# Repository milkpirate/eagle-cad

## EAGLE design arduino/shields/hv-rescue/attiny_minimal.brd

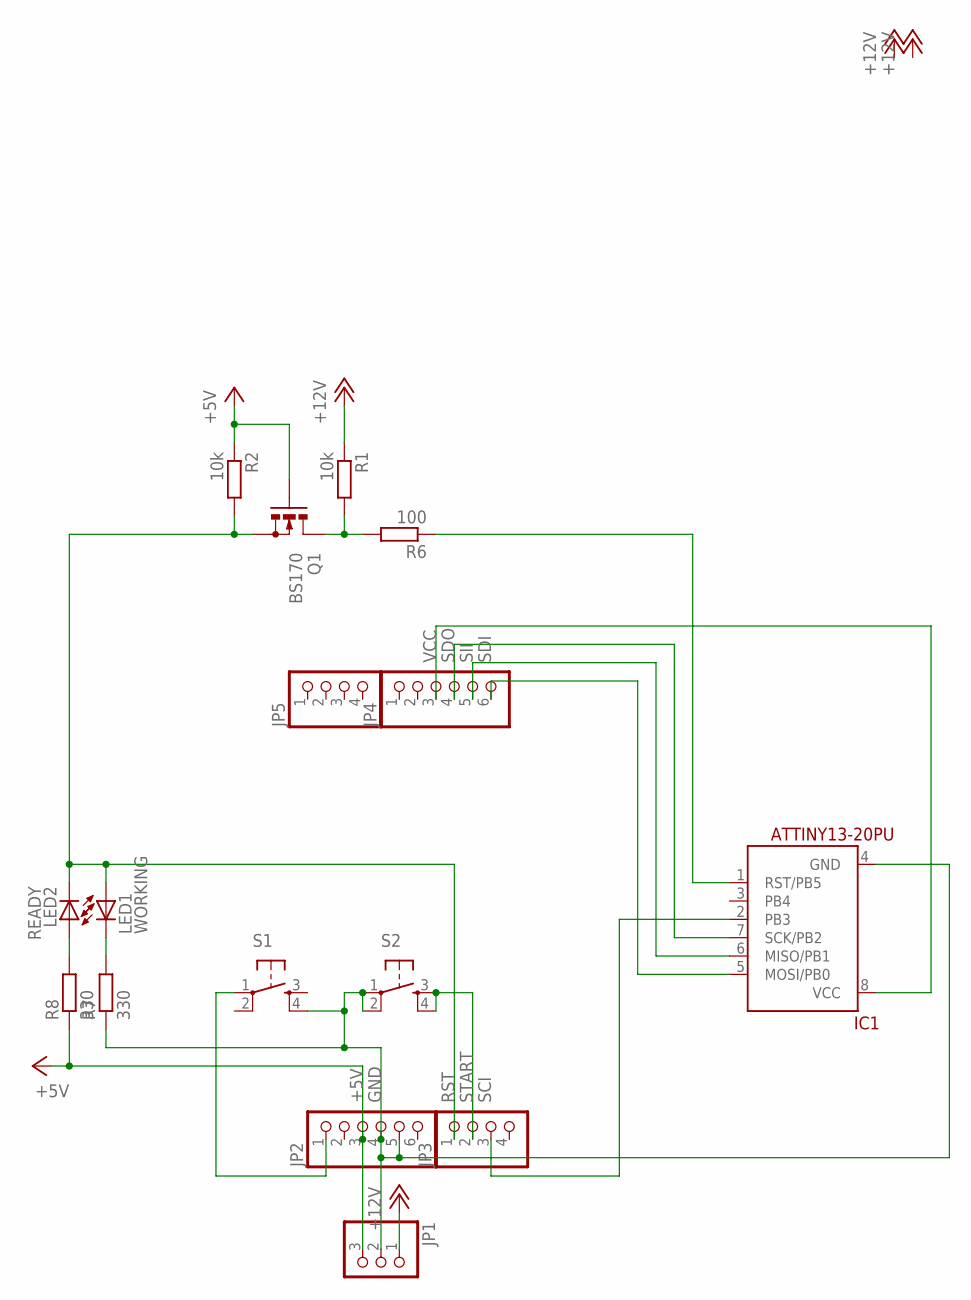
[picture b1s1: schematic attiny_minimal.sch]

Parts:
IC1: ATTINY13-20PU; DIL08
JP1: PINHD-1X3/90; 1X03/90
JP2, JP4: PINHD-1X6; 1X06
JP3, JP5: PINHD-1X4; 1X04
LED1: WORKING; LED3MM
LED2: READY; LED3MM
Q1: BS170; SOT54E
R1: 10k; 0207/2V
R2: 10k; 0204/7
R6: 100; 0204/7
R7, R8: 330; 0207/2V
S1, S2: TAC_SWITCHPTH; TACTILE-PTH

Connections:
+5V: JP1.3, JP2.3, Q1.G, R2.1, R8.1
+12V: JP1.1, R1.1
GND: IC1.4 (GND), JP1.2, JP2.4, JP2.5, R7.1, S1.4, S2.1, S2.2
unnamed: JP2.1, S1.1
unnamed: LED1.K (C), R7.2
unnamed: LED2.A, R8.2
unnamed: Q1.D, R1.2, R6.2
unnamed: IC1.1 (RST/PB5), R6.1
RST: JP3.1, LED1.A, LED2.K (C), Q1.S, R2.2
SCI: IC1.2 (PB3), JP3.3
SDI: IC1.5 (MOSI/PB0), JP4.6
SDO: IC1.7 (SCK/PB2), JP4.4
SII: IC1.6 (MISO/PB1), JP4.5
START: JP3.2, S2.3, S2.4
VCC: IC1.8 (VCC), JP4.3

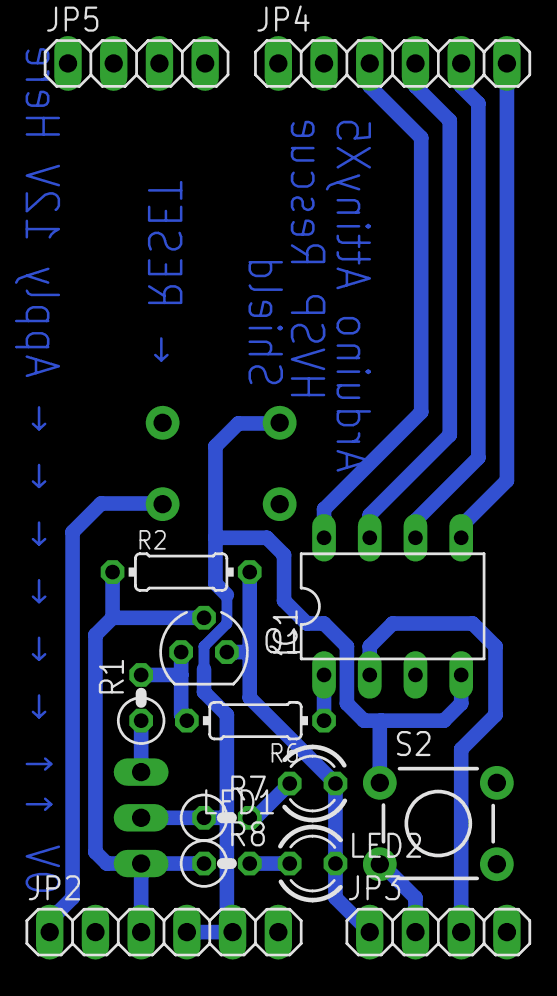
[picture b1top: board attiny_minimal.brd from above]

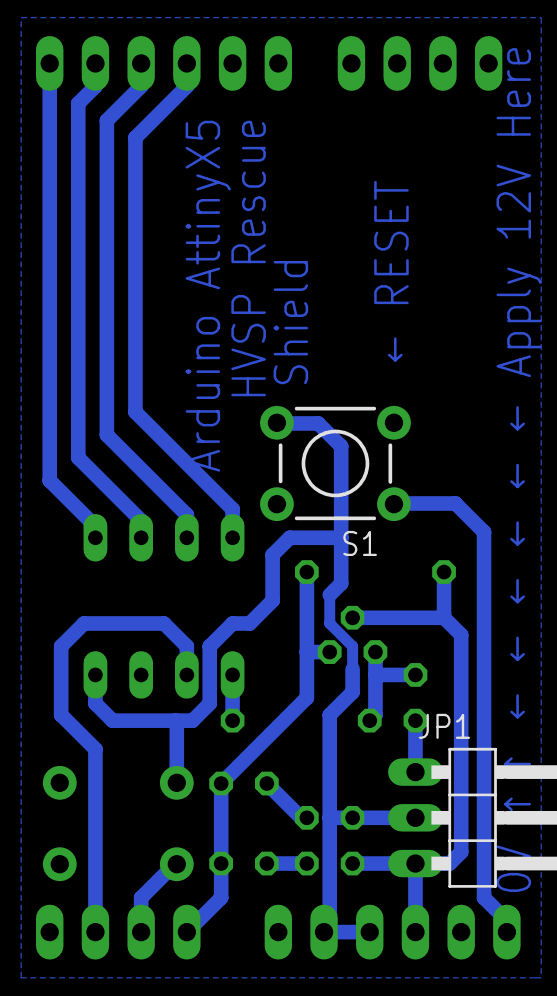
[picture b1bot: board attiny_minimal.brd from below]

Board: 2 copper layers, 16 parts (2 on the bottom side), 15 nets.

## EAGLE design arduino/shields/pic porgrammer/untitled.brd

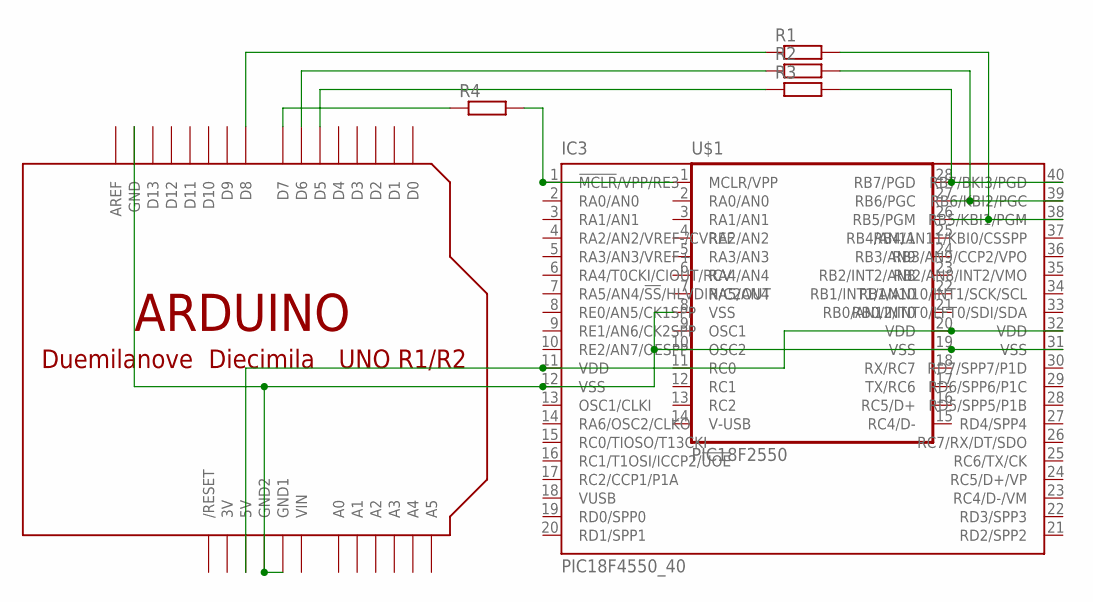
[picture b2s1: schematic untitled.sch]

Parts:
IC3: PIC18F4550_40; DIL40
R1, R2, R3, R4: R-EU_0204/7; 0204/7
U$1: PIC18F2550; DIL28-3
U$2: ARDUINO-NOHOLE

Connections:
3V: U$2.3V
GND: IC3.12 (VSS), IC3.31 (VSS), U$1.8 (VSS), U$1.19 (VSS), U$2.GND, U$2.GND1, U$2.GND2
unnamed: IC3.1 (!MCLR!/VPP/RE3), R4.2, U$1.1 (MCLR/VPP)
unnamed: IC3.40 (RB7/BKI3/PGD), R3.2, U$1.28 (RB7/PGD)
unnamed: IC3.39 (RB6/KBI2/PGC), R2.2, U$1.27 (RB6/PGC)
unnamed: IC3.38 (RB5/KBI1/PGM), R1.2, U$1.26 (RB5/PGM)
unnamed: IC3.11 (VDD), IC3.32 (VDD), U$1.20 (VDD), U$2.5V
unnamed: R1.1, U$2.D8
unnamed: R2.1, U$2.D6
unnamed: R3.1, U$2.D5
unnamed: R4.1, U$2.D7
VIN: U$2.VIN

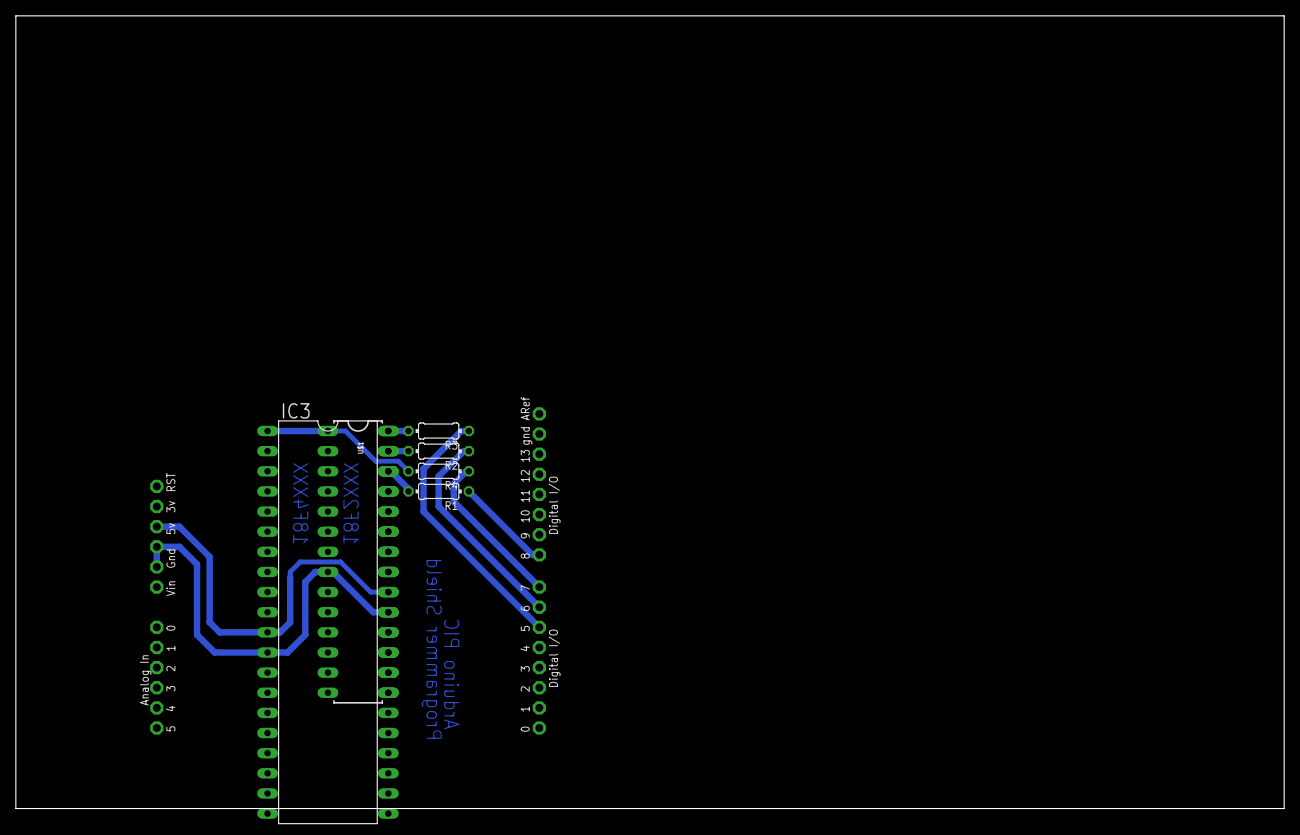
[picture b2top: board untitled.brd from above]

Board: 2 copper layers, 160.0 x 100.0 mm, 7 parts (0 on the bottom side), 10 nets.

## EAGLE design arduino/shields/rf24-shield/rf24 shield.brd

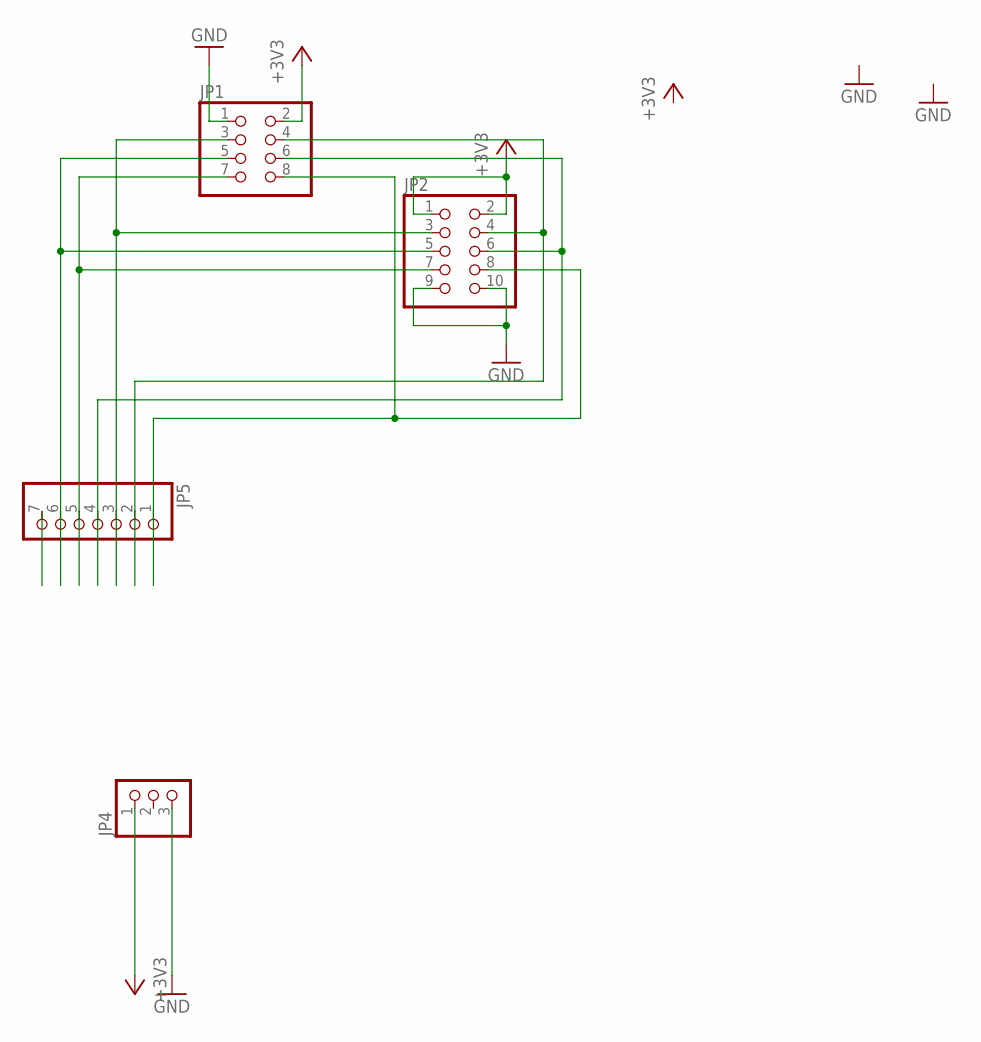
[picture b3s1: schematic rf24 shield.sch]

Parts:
JP1: PINHD-2X4; 2X04
JP2: PINHD-2X5; 2X05
JP4: PINHD-1X3; 1X03
JP5: PINHD-1X7; 1X07

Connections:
+3V3: JP1.2, JP2.1, JP2.2, JP4.1
GND: JP1.1, JP2.9, JP2.10, JP4.3
unnamed: JP1.3, JP2.3, JP5.3
unnamed: JP1.5, JP2.5, JP5.6
unnamed: JP1.7, JP2.7, JP5.5
unnamed: JP1.4, JP2.4, JP5.2
unnamed: JP1.6, JP2.6, JP5.4
unnamed: JP1.8, JP2.8, JP5.1

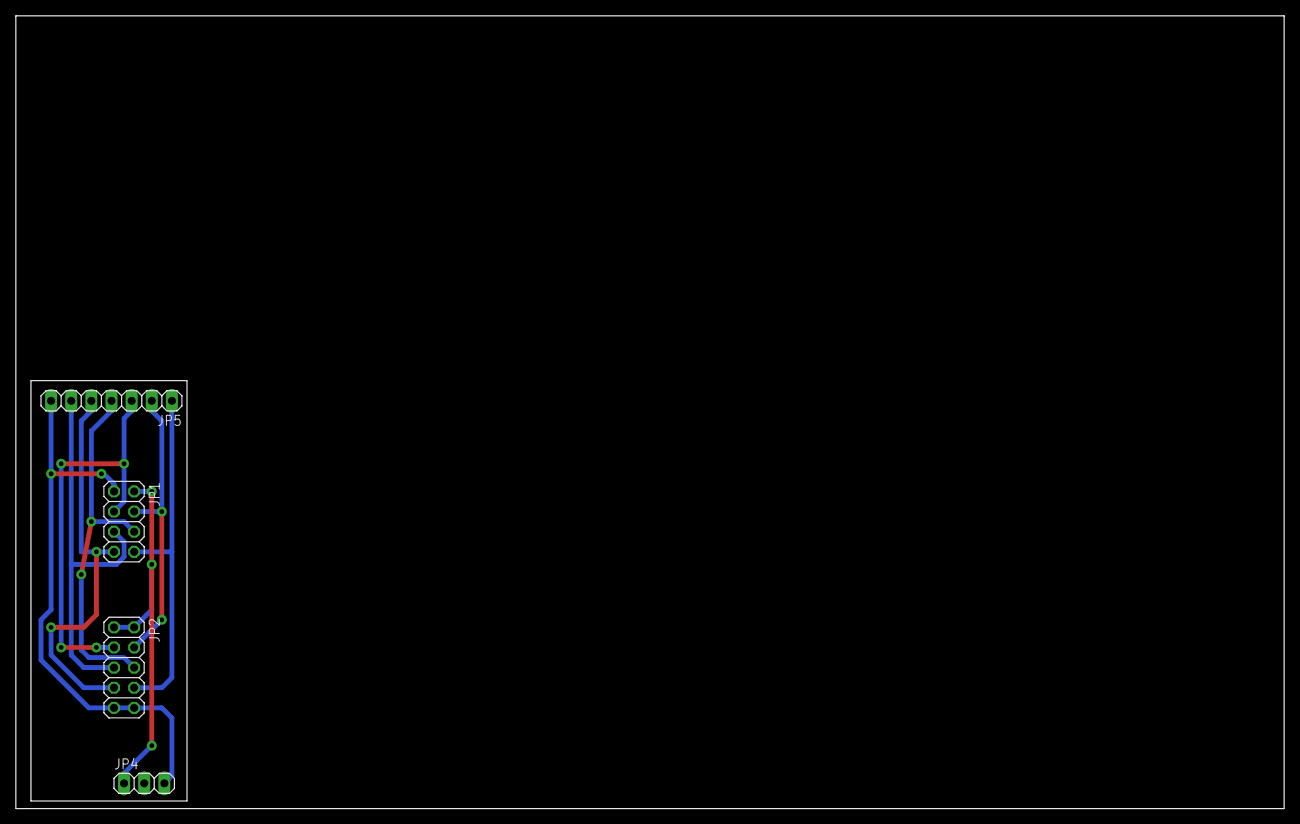
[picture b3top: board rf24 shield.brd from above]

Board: 2 copper layers, 160.0 x 100.0 mm, 4 parts (0 on the bottom side), 8 nets.

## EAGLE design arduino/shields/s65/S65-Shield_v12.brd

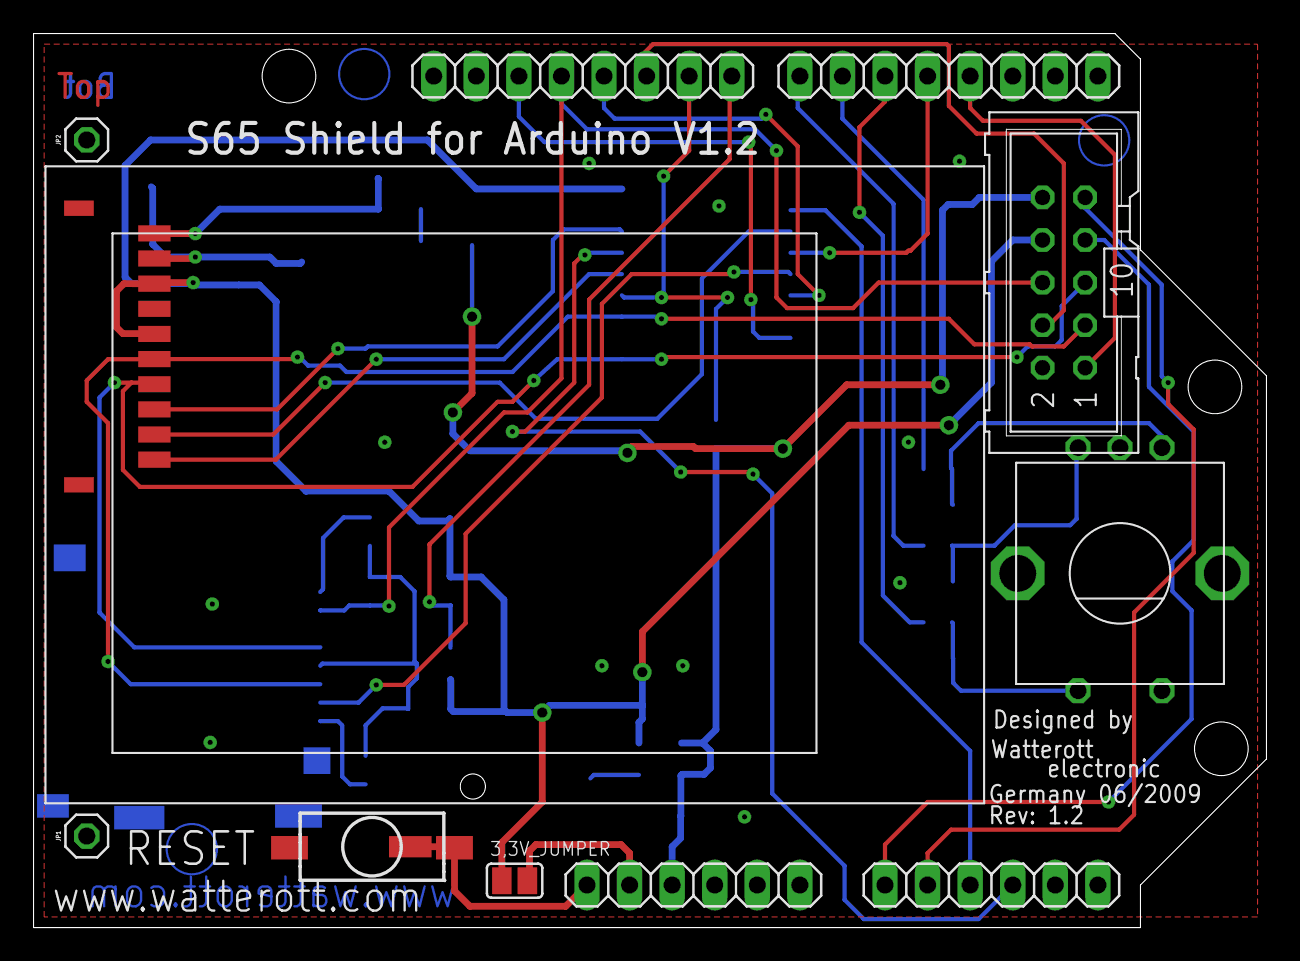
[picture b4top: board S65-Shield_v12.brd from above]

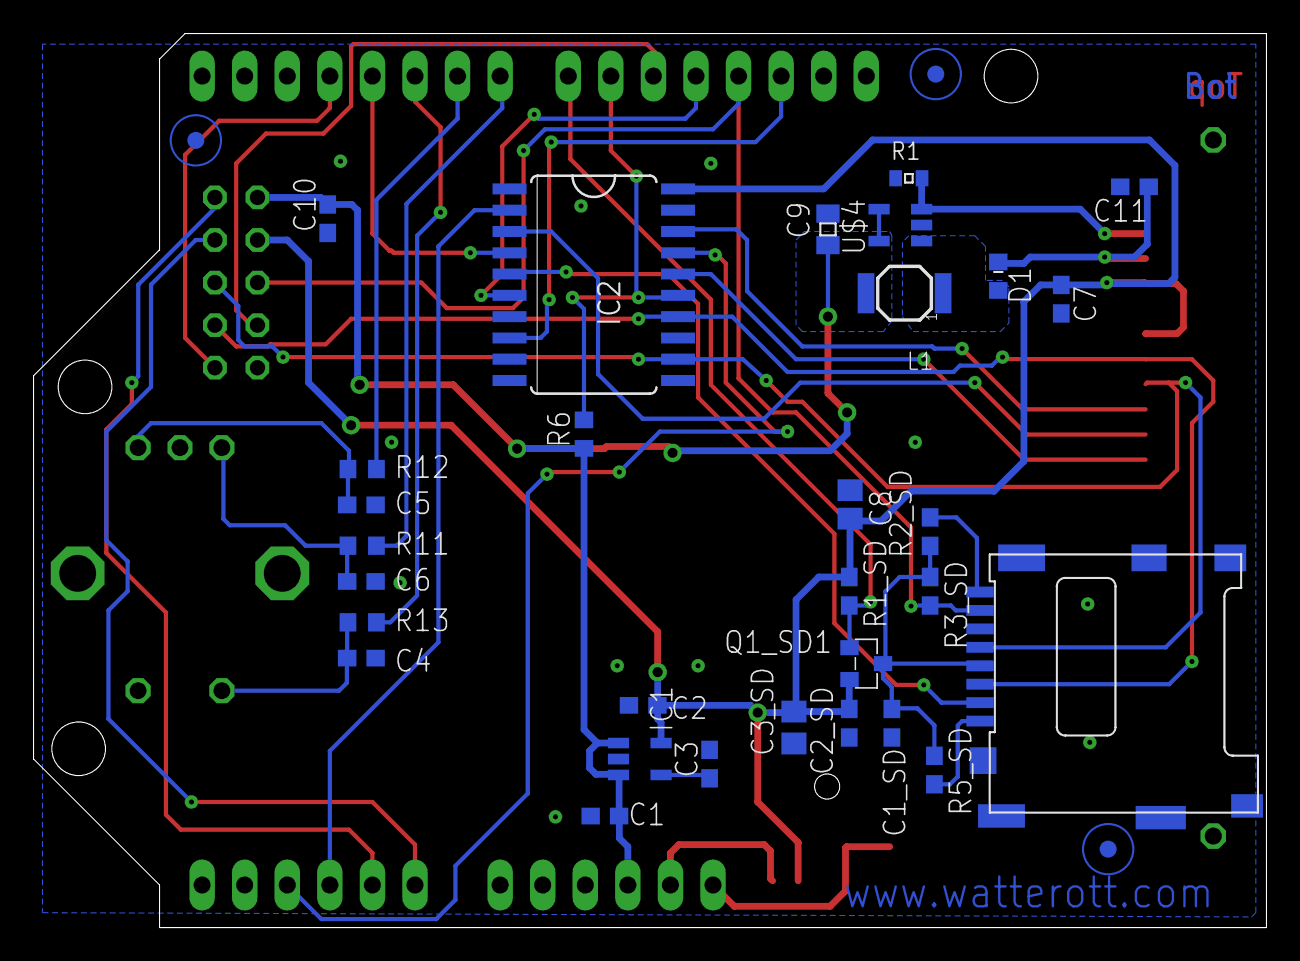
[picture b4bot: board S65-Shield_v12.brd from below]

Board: 2 copper layers, 73.6 x 53.3 mm, 45 parts (33 on the bottom side), 36 nets.

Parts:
3,3V_JUMPER: SJ
.: SMD1,27-2,54
C1, C1_SD, C2, C2_SD, C7: 100nF; C0603
C3: 10nF; C0603
C3_SD: 2,2µF; C0805
C4, C5, C6: nM; C0603
C8: 100nF; C0805
C9: 2,2µF; 0805
C10, C11: 1µ; C0603
D1: miniSchottky; D0603
IC1: LP2985; SOT23-5
IC2: 74LVC244; SO20W
J1, J3: 1X08
J2: 1X06
JP1, JP2: 1X01
L1: 33µH; MS42
LCD1: S65
POWER: 1X06
Q1_SD1: P-CHN; MICRO3
R1: 100; 0603
R1_SD, R2_SD, R3_SD, R5_SD: 47k; R0603
R6: 10k; R0603
R11, R12, R13: 1k; R0603
RESET: TAST_SMD1; SMD_TASTER
SD: MICRO-SD
SV1: ML10
SW1: EC12E_SW; ALPS_EC12E_SW
U$1, U$2, U$3: FIDUCIALMOUNT; FIDUCIA-MOUNT
U$4: LM2705; SOT23-5

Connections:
3: J1.4, SV1.1
4: IC2.4, J1.5
5: J1.6, R13.1
6: J1.7, R12.1
7: J1.8, R11.1
8: J3.1, Q1_SD1.1, R1_SD.2
9: IC2.15, J3.2, R6.2
+3V3: 3,3V_JUMPER.1, C2.1, C2_SD.2, C3_SD.2, C7.1, C8.1, IC1.5, IC2.20, LCD1.1V8, LCD1.2V9, Q1_SD1.2, R1_SD.1, SV1.8
+5V: C1.1, C9.2, C10.2, IC1.1, IC1.3, L1.1, POWER.3, R6.1, SV1.10, U$4.4, U$4.5
A0: J2.1, SV1.7
A1: J2.2, SV1.9
A2: IC2.2, J2.3
A3: IC2.17, J2.4
GND: C1.2, C1_SD.2, C2.2, C2_SD.1, C3.2, C3_SD.1, C4.2, C5.2, C6.2, C7.2, C8.2, C9.1, C10.1, C11.2, IC1.2, IC2.1, IC2.10, IC2.11, IC2.13, IC2.19, J3.7, LCD1.GND, POWER.4, POWER.5, R1.1, RESET.1, SD.6, SV1.2, SW1.C, SW1.D, U$4.2
LED+: C11.1, D1.1, LCD1.LED+
LED-: LCD1.LED-, R1.2, U$4.3
LL_MOSI: IC2.14, LCD1.DATA, SD.3, SV1.3
LL_SCK: IC2.12, LCD1.CLK, SD.5, SV1.5
MISO: J3.5, R3_SD.2, SD.7, SV1.6
MOSI: IC2.6, J3.4
unnamed: R5_SD.2, SD.1
unnamed: IC2.16, LCD1.RS
unnamed: IC2.18, LCD1.CS
unnamed: IC2.3, LCD1.RESET
unnamed: D1.2, L1.2, U$4.1
unnamed: C4.1, R13.2, SW1.E
unnamed: C5.1, R12.2, SW1.A
unnamed: C6.1, R11.2, SW1.B
unnamed: C3.1, IC1.4
unnamed: ..1, POWER.1, RESET.2
unnamed: R2_SD.2, SD.8
SCK: IC2.8, J3.6
SD_3V3: C1_SD.1, Q1_SD1.3, R2_SD.1, R3_SD.1, R5_SD.1, SD.4
SD_CS: IC2.5, SD.2
SS: J3.3, SV1.4
VCC3O: 3,3V_JUMPER.2, POWER.2

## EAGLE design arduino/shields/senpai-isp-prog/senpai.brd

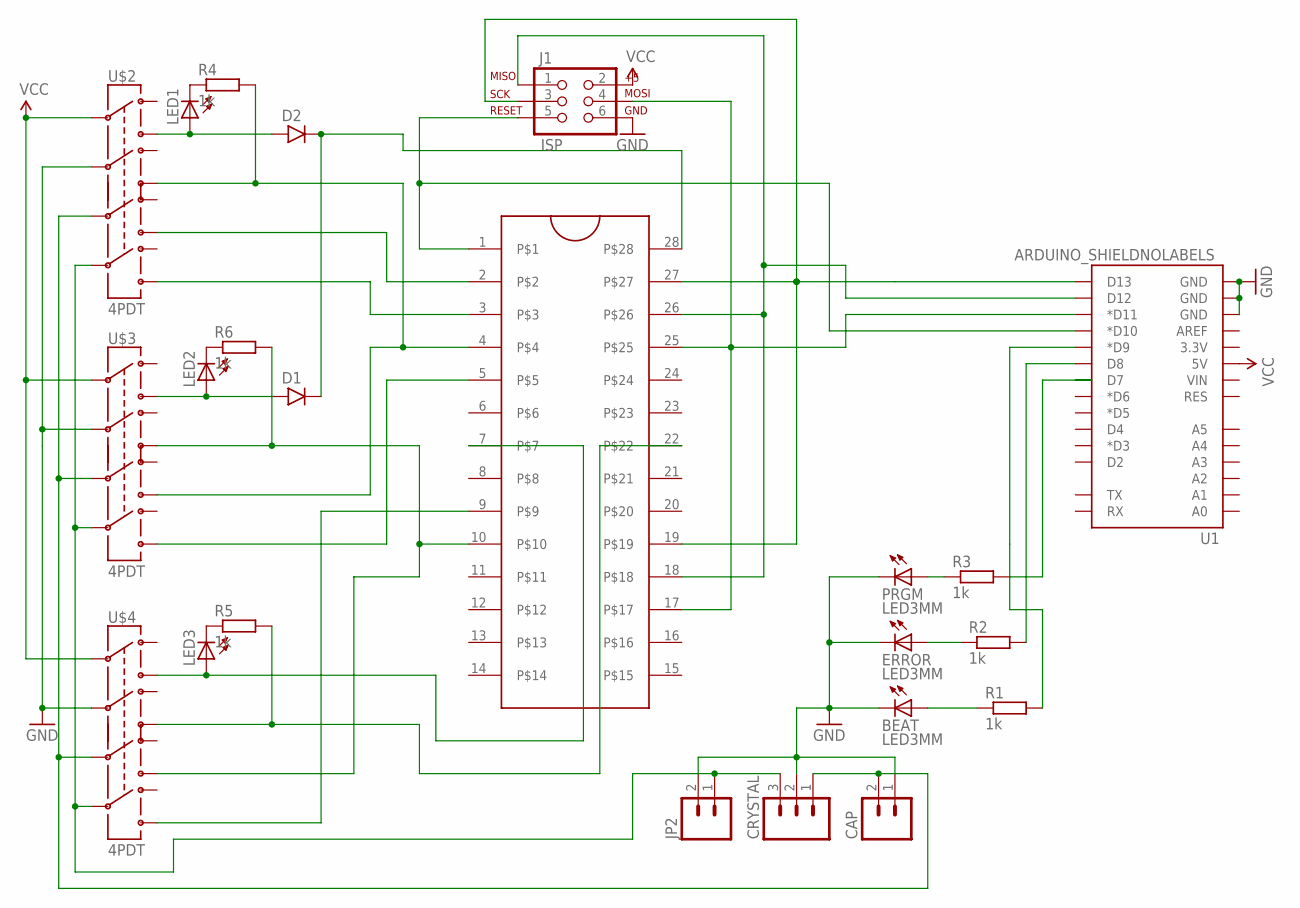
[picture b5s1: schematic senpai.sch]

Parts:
BEAT: LED3MM; LED5MM
CAP: M02PTH; 1X02
CRYSTAL: M03LOCK; 1X03_LOCK
D1, D2: DO41.2; DO41-2
ERROR: LED3MM; LED5MM
J1: ISP; 2X3
JP2: M02PTH; 1X02
LED1, LED2, LED3: LED5MM
PRGM: LED3MM; LED5MM
R1, R2, R3, R4, R5, R6: 1k; 0204/7
U1: ARDUINO_SHIELDNOLABELS; DUEMILANOVE_SHIELD_NOLABELS
U$1: ZIFSOCKET-28-3ZIFFSOCKET-28-3; DIL28-3-ZIF_SOCKET
U$2, U$3, U$4: 4PDT

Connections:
GND: BEAT.K (C), CAP.1, CRYSTAL.2, ERROR.K (C), J1.6, JP2.2, PRGM.K (C), U1.GND@0 (GND), U1.GND@1 (GND), U1.GND@2 (GND), U$2.5, U$3.5, U$4.5
unnamed: J1.4, U1.D11 (*D11), U$1.17, U$1.25
unnamed: J1.1, U1.D12, U$1.18, U$1.26
unnamed: J1.3, U1.D13, U$1.19, U$1.27
unnamed: J1.5, U1.D10 (*D10), U$1.1
unnamed: CAP.2, CRYSTAL.1, U$2.8, U$3.8, U$4.8
unnamed: CRYSTAL.3, JP2.1, U$2.11, U$3.11, U$4.11
unnamed: LED3.K (C), R5.1
unnamed: R5.2, U$1.22, U$4.6
unnamed: LED1.K (C), R4.1
unnamed: BEAT.A, R1.1
unnamed: ERROR.A, R2.1
unnamed: PRGM.A, R3.1
unnamed: D1.A, LED2.A, U$3.3
unnamed: D2.A, LED1.A, U$2.3
unnamed: R4.2, U$1.4, U$2.6, U$3.9
unnamed: R1.2, U1.D9 (*D9)
unnamed: R2.2, U1.D8
unnamed: R3.2, U1.D7
unnamed: U$1.2, U$2.9
unnamed: U$1.3, U$2.12
unnamed: R6.2, U$1.10, U$3.6, U$4.9
unnamed: D1.C, D2.C, U$1.28
unnamed: U$1.5, U$3.12
unnamed: LED3.A, U$1.7, U$4.3
unnamed: U$1.9, U$4.12
unnamed: LED2.K (C), R6.1
VCC: J1.2, U1.5V, U$2.2, U$3.2, U$4.2

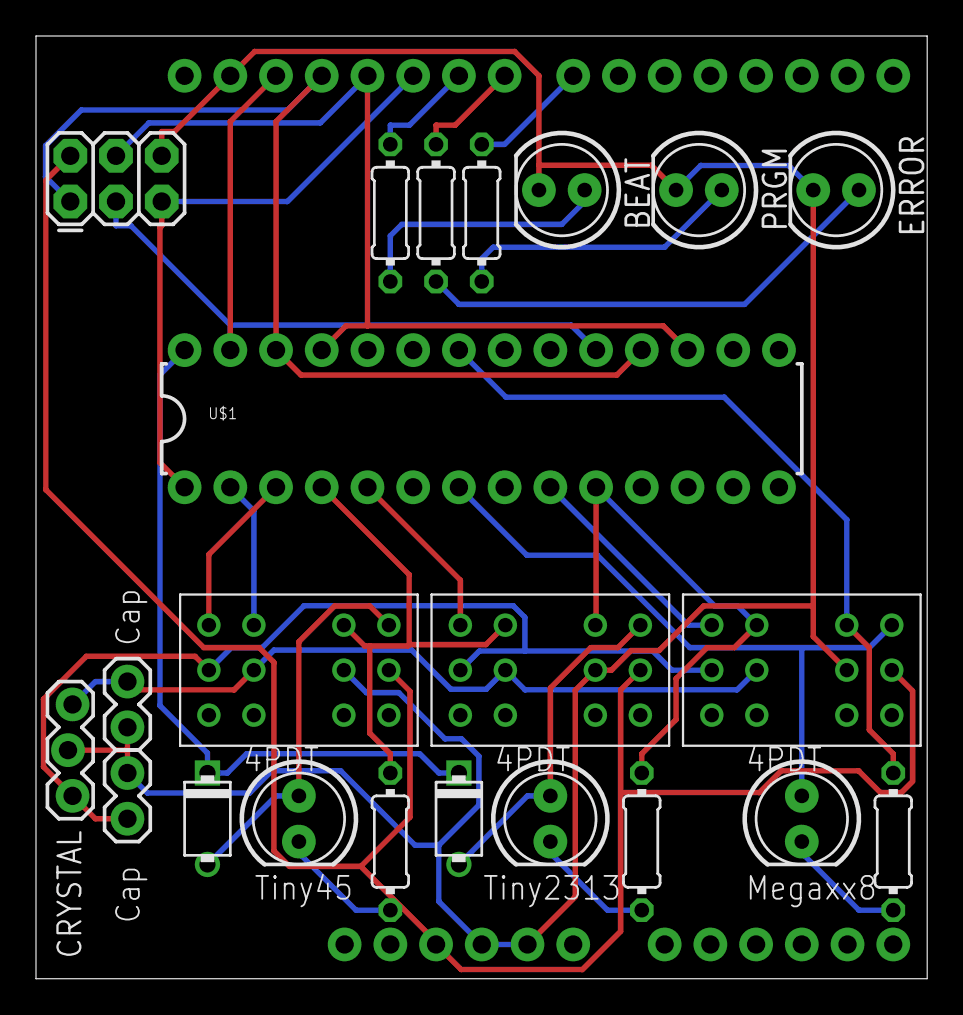
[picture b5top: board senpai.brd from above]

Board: 2 copper layers, 49.5 x 52.4 mm, 23 parts (0 on the bottom side), 28 nets.

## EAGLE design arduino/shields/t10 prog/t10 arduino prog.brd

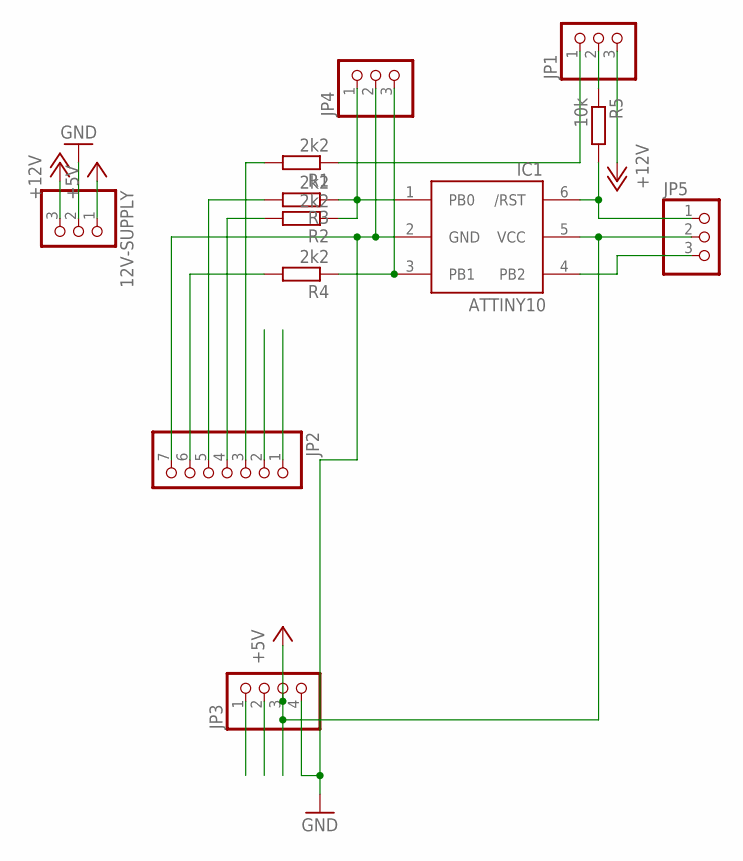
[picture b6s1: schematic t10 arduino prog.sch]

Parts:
12V-SUPPLY: PINHD-1X3/90; 1X03/90
IC1: ATTINY10; SOT23-6
JP1, JP4, JP5: PINHD-1X3; 1X03
JP2: PINHD-1X7; 1X07
JP3: PINHD-1X4; 1X04
R1, R2, R3, R4: 2k2; 0207/2V
R5: 10k; 0207/2V

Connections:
+5V: 12V-SUPPLY.1, IC1.5 (VCC), JP3.3, JP5.2
+12V: 12V-SUPPLY.3, JP1.3
GND: 12V-SUPPLY.2, IC1.2 (GND), JP2.7, JP3.4, JP4.2
unnamed: JP1.2, R5.1
unnamed: JP2.3, R1.2
unnamed: JP2.4, R2.2
unnamed: JP2.5, R3.2
unnamed: JP2.6, R4.2
unnamed: IC1.1 (PB0), JP4.1, R2.1, R3.1
unnamed: IC1.3 (PB1), JP4.3, R4.1
unnamed: JP1.1, R1.1
unnamed: IC1.6 (/RST), JP5.1, R5.2
unnamed: IC1.4 (PB2), JP5.3

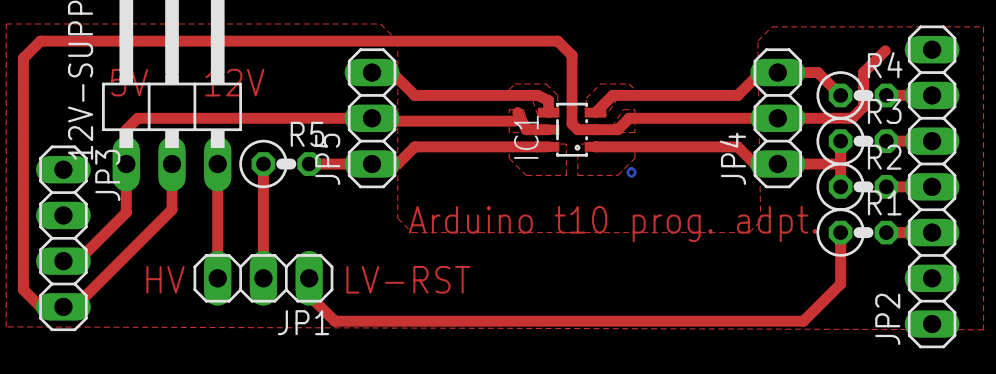
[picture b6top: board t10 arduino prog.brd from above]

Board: 2 copper layers, 12 parts (0 on the bottom side), 13 nets.

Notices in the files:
parts and their libraries:
SparkFun: Licensing: CC v3.0 Share-Alike You are welcome to use this library for commercial purposes.
